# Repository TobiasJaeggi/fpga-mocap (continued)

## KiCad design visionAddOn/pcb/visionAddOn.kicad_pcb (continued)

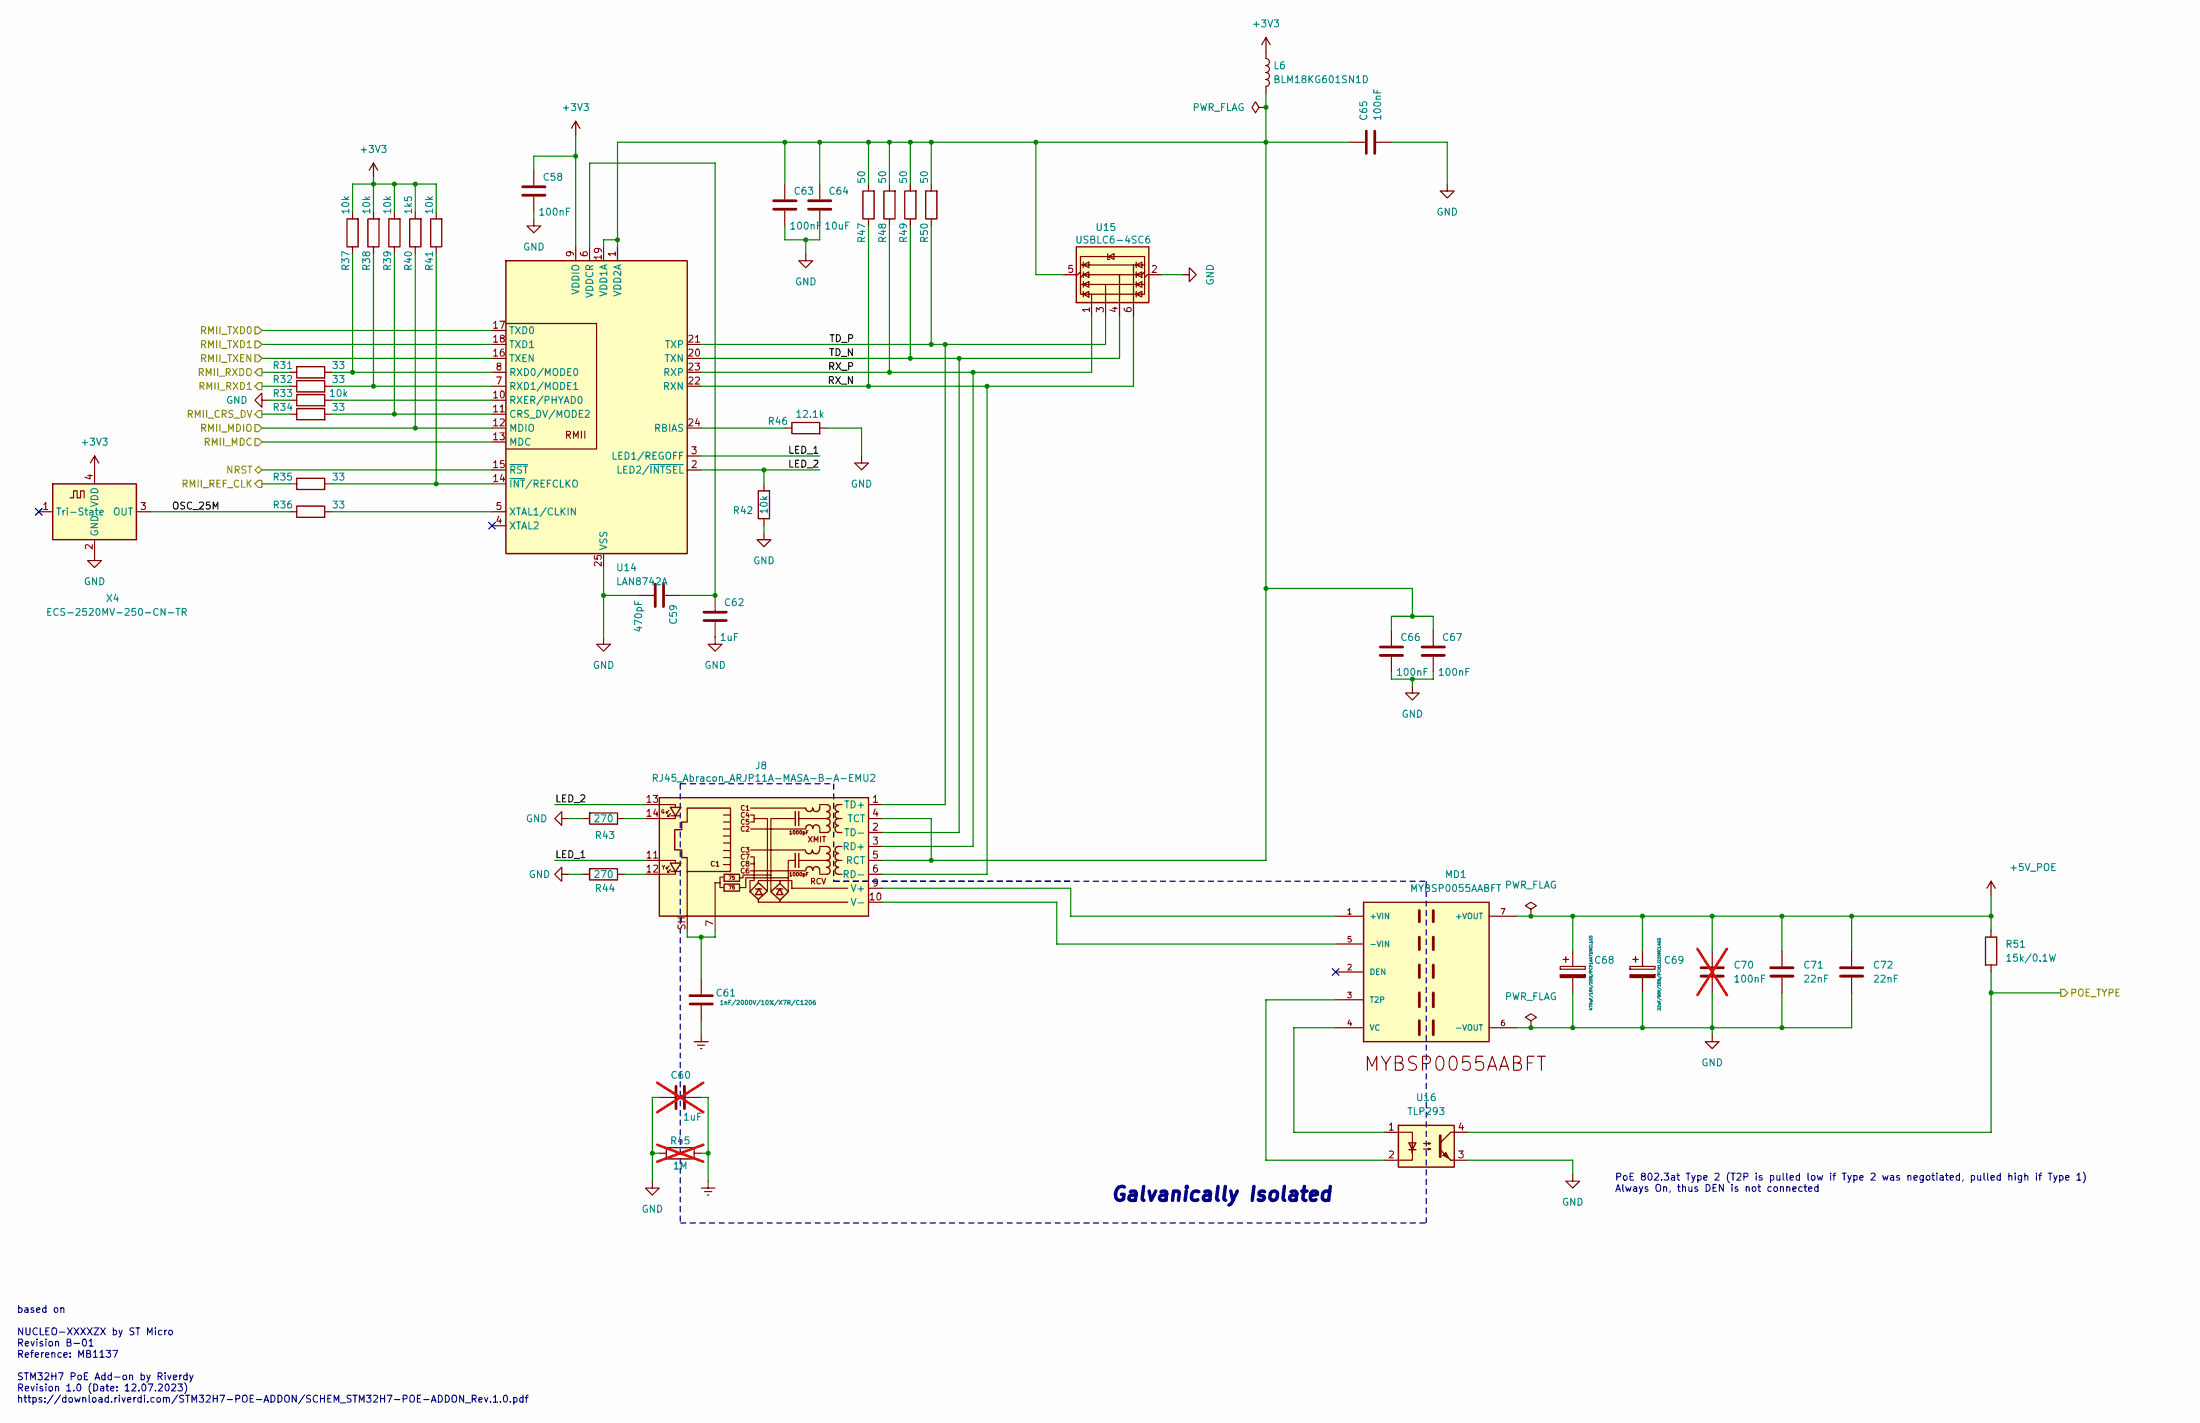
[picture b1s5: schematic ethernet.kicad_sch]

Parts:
C58, C63, C65, C66, C67: 100nF; C_0402_1005Metric; DigiKey-Partnumber 490-6328-2-ND
C59: 470pF; C_0402_1005Metric; DigiKey-Partnumber 490-1300-2-ND
C60: 1uF; C_0402_1005Metric; DigiKey-Partnumber 490-10024-2-ND; not fitted
C61: 1nF/2000V/10%/X7R/C1206; C_1206_3216Metric; DigiKey-Partnumber 709-VPDD202W102K1GV001ETR-ND
C62: 1uF; C_0402_1005Metric; DigiKey-Partnumber 490-10024-2-ND
C64: 10uF; C_0402_1005Metric; DigiKey-Partnumber 490-GRM155R61A106ME11DTR-ND
C68: 470uF/10V/20%/PCF1A471MCL1GS; CP_Elec_10x10; DigiKey-Partnumber 493-2996-2-ND
C69: 22uF/80V/20%/PCH1J220MCL4GS; CP_Elec_6.3x7.7; DigiKey-Partnumber PCH1J220MCL4GTR-ND
C70: 100nF; C_0603_1608Metric; DigiKey-Partnumber 311-1088-2-ND; not fitted
C71, C72: 22nF; C_0603_1608Metric; DigiKey-Partnumber 490-17777-2-ND
J8: RJ45_Abracon_ARJP11A-MASA-B-A-EMU2; RJ45_Abracon_ARJP11A-MA_Horizontal; DigiKey-Partnumber ARJP11A-MASA-B-A-EMU2-ND
L6: BLM18KG601SN1D; L_0603_1608Metric; DigiKey-Partnumber 490-5258-2-ND
MD1: MYBSP0055AABFT; MYBSP0055AABFT_0; DigiKey-Partnumber 811-MYBSP0055AABFTTR-ND
R31, R32, R34, R35, R36: 33; R_0402_1005Metric; DigiKey-Partnumber 311-33.0LRTR-ND
R33, R37, R38, R39, R41, R42: 10k; R_0402_1005Metric; DigiKey-Partnumber 311-10KJRTR-ND
R40: 1k5; R_0402_1005Metric; DigiKey-Partnumber 311-1.5KJRTR-ND
R43, R44: 270; R_0402_1005Metric; DigiKey-Partnumber 541-4842-2-ND
R45: 1M; R_0402_1005Metric; DigiKey-Partnumber 311-1.00MLRTR-ND; not fitted
R46: 12.1k; R_0402_1005Metric; DigiKey-Partnumber 311-12.1KLRTR-ND
R47, R48, R49, R50: 50; R_0402_1005Metric; DigiKey-Partnumber 13-RT0402BRE0750RLTR-ND
R51: 15k/0.1W; R_0402_1005Metric; DigiKey-Partnumber P15.0KLTR-ND
U14: LAN8742A; VQFN-24-1EP_4x4mm_P0.5mm_EP2.5x2.5mm_ThermalVias; DigiKey-Partnumber LAN8742A-CZ-TR-ND
U15: USBLC6-4SC6; SOT-23-6; DigiKey-Partnumber 497-4492-2-ND
U16: TLP293; SOIC-4_4.55x2.6mm_P1.27mm; DigiKey-Partnumber TLP293(GB-TPLETR-ND
X4: ECS-2520MV-250-CN-TR; Oscillator_SMD_ECS_2520MV-xxx-xx-4Pin_2.5x2.0mm; DigiKey-Partnumber XC2752TR-ND

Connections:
+3V3: C58.2, L6.1, R37.2, R38.2, R39.2, R40.2, R41.2, U14.9 (VDDIO), X4.4 (VDD); also elsewhere on the board
+5V_POE: C68.1, C69.1, C70.1, C71.1, C72.1, MD1.7 (+VOUT), R51.1; also elsewhere on the board
/N_RESET: U14.15 (~RST); also elsewhere on the board
/ethernet/LED_1: J8.11, U14.3 (LED1/REGOFF)
/ethernet/LED_2: J8.13, R42.2, U14.2 (LED2/~INTSEL)
/ethernet/OSC_25M: R36.1, X4.3 (OUT)
/ethernet/POE_TYPE: R51.2, U16.4; also elsewhere on the board
/ethernet/RMII_CRS_DV: R34.1; also elsewhere on the board
/ethernet/RMII_MDC: U14.13 (MDC); also elsewhere on the board
/ethernet/RMII_MDIO: R40.1, U14.12 (MDIO); also elsewhere on the board
/ethernet/RMII_REF_CLK: R35.1; also elsewhere on the board
/ethernet/RMII_RXD1: R32.1; also elsewhere on the board
/ethernet/RMII_RXDO: R31.1; also elsewhere on the board
/ethernet/RMII_TXD0: U14.17 (TXD0); also elsewhere on the board
/ethernet/RMII_TXD1: U14.18 (TXD1); also elsewhere on the board
/ethernet/RMII_TXEN: U14.16 (TXEN); also elsewhere on the board
/ethernet/RX_N: J8.6 (RD-), R47.1, U14.22 (RXN), U15.6 (I/O4)
/ethernet/RX_P: J8.3 (RD+), R48.1, U14.23 (RXP), U15.1 (I/O1)
/ethernet/TD_N: J8.2 (TD-), R49.1, U14.20 (TXN), U15.4 (I/O3)
/ethernet/TD_P: J8.1 (TD+), R50.1, U14.21 (TXP), U15.3 (I/O2)
Earth: C60.1, C61.1, R45.1
GND: C58.1, C59.1, C60.2, C62.1, C63.1, C64.1, C65.2, C66.1, C67.1, C68.2, C69.2, C70.2, C71.2, C72.2, MD1.6 (-VOUT), R33.1, R42.1, R43.2, R44.2, R45.2, R46.2, U14.25 (VSS), U15.2 (GND), U16.3, X4.2 (GND); also elsewhere on the board
unnamed: C61.2, J8.7, J8.SH
unnamed: J8.12, R44.1
unnamed: J8.14, R43.1
unnamed: C63.2, C64.2, C65.1, C66.2, C67.2, J8.4 (TCT), J8.5 (RCT), L6.2, R47.2, R48.2, R49.2, R50.2, U14.1 (VDD2A), U14.19 (VDD1A), U15.5 (VBUS)
unnamed: J8.9 (V+), MD1.1 (+VIN)
unnamed: J8.10 (V-), MD1.5 (-VIN)
unnamed: MD1.3 (T2P), U16.2
unnamed: MD1.4 (VC), U16.1
unnamed: R34.2, R39.1, U14.11 (CRS_DV/MODE2)
unnamed: R46.1, U14.24 (RBIAS)
unnamed: R31.2, R37.1, U14.8 (RXD0/MODE0)
unnamed: R32.2, R38.1, U14.7 (RXD1/MODE1)
unnamed: R33.2, U14.10 (RXER/PHYAD0)
unnamed: C59.2, C62.2, U14.6 (VDDCR)
unnamed: R36.2, U14.5 (XTAL1/CLKIN)
unnamed: R35.2, R41.1, U14.14 (~INT/REFCLKO)

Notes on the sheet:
PoE 802.3at Type 2 (T2P is pulled low if Type 2 was negotiated, pulled high if Type 1) Always On, thus DEN is not connected
Galvanically Isolated
based on NUCLEO-XXXXZX by ST Micro Revision B-01 Reference: MB1137 STM32H7 PoE Add-on by Riverdy Revision 1.0 (Date: 12.07.2023) https://download.riverdi.com/STM32H7-POE-ADDON/SCHEM_STM32H7-POE-ADDON_Rev.1.0.pdf

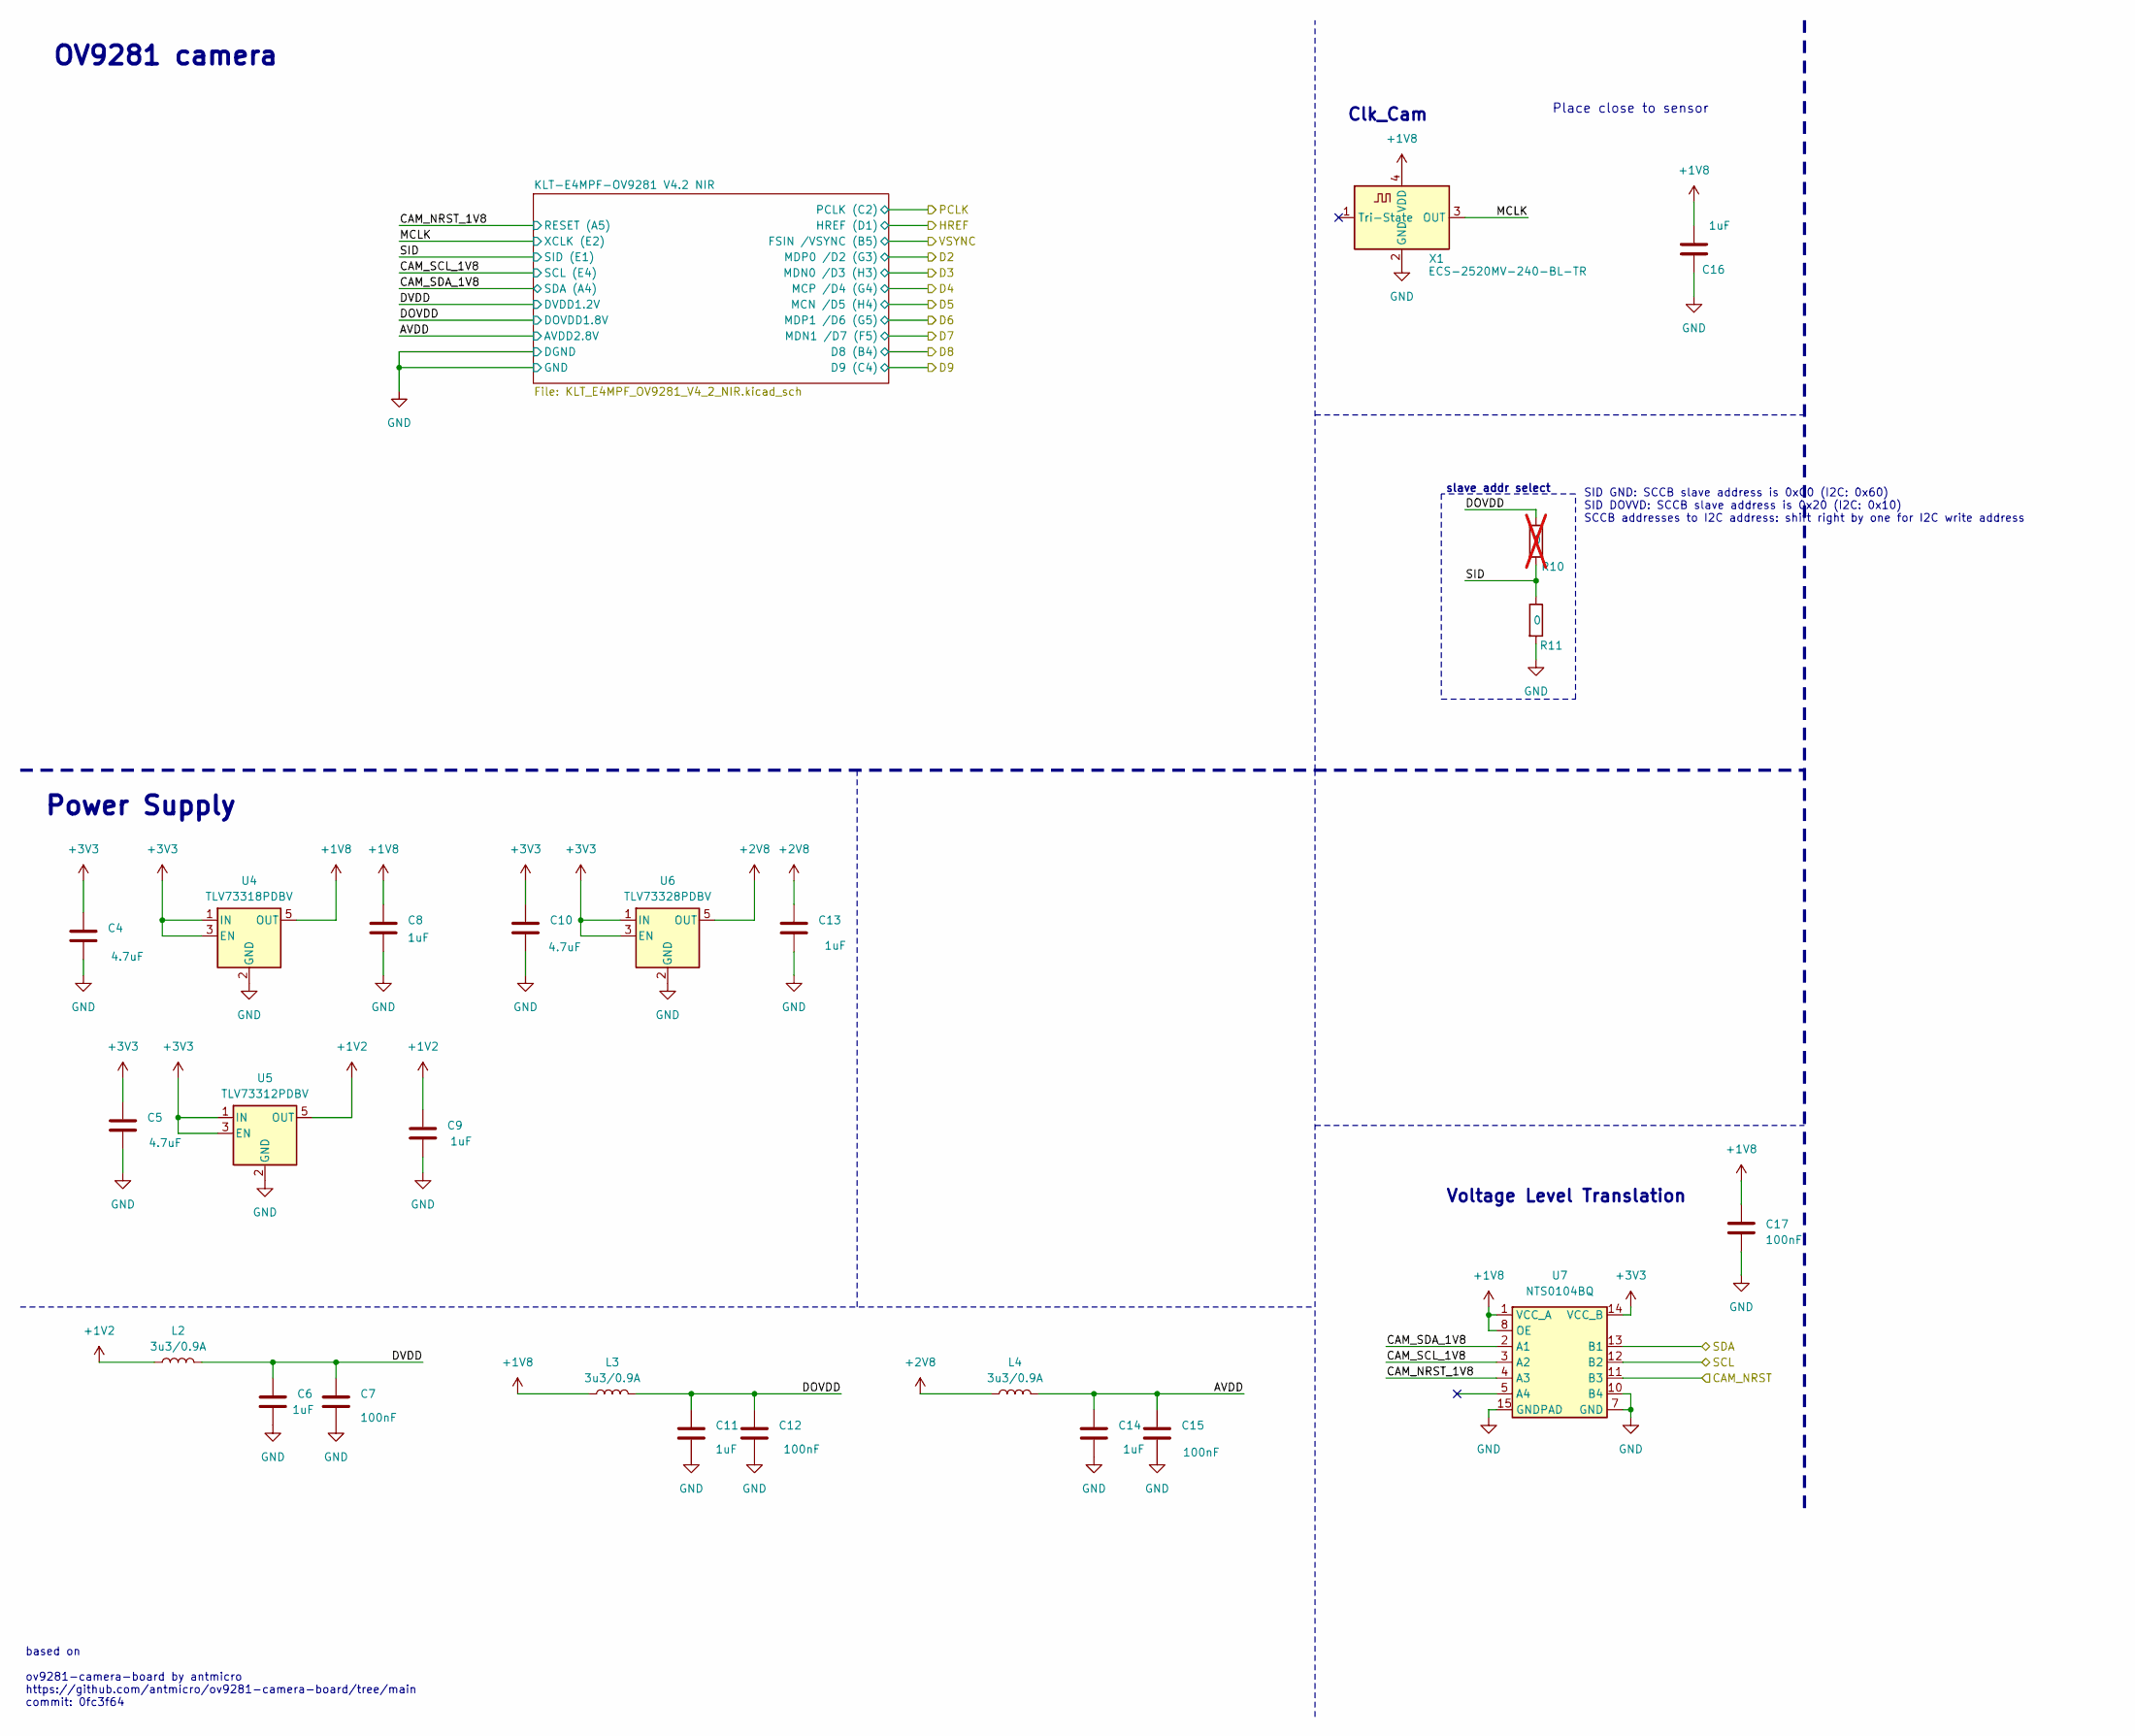
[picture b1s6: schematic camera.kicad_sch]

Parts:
C4, C5, C10: 4.7uF; C_0805_2012Metric; DigiKey-Partnumber 1292-0805X475K250CTTR-ND
C6, C8, C9, C11, C13, C14, C16: 1uF; C_0603_1608Metric; DigiKey-Partnumber 445-4112-2-ND
C7, C12, C15, C17: 100nF; C_0402_1005Metric; DigiKey-Partnumber 490-6328-2-ND
L2, L3, L4: MLP2012S3R3MT; L_0805_2012Metric; DigiKey-Partnumber 445-6365-2-ND
R10: 0; R_0402_1005Metric; DigiKey-Partnumber 311-0.0JRTR-ND; not fitted
R11: 0; R_0402_1005Metric; DigiKey-Partnumber 311-0.0JRTR-ND
U4: TLV73318PDBV; SOT-23-5; DigiKey-Partnumber 296-40669-2-ND
U5: TLV73312PDBV; SOT-23-5; DigiKey-Partnumber 296-40665-2-ND
U6: TLV73328PDBV; SOT-23-5; DigiKey-Partnumber 296-42282-2-ND
U7: NTS0104BQ; DHVQFN-14-1EP_2.5x3mm_P0.5mm_EP1x1.5mm; DigiKey-Partnumber 568-12382-2-ND
X1: ECS-2520MV-240-BL-TR; Oscillator_SMD_ECS_2520MV-xxx-xx-4Pin_2.5x2.0mm; DigiKey-Partnumber 50-ECS-2520MV-240-BL-TR-ND

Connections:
+1V2: C9.1, L2.1, U5.5 (OUT)
+1V8: C8.1, C16.1, C17.1, L3.1, U4.5 (OUT), U7.1 (VCC_A), U7.8 (OE), X1.4 (VDD)
+2V8: C13.1, L4.1, U6.5 (OUT)
+3V3: C4.1, C5.1, C10.1, U4.1 (IN), U4.3 (EN), U5.1 (IN), U5.3 (EN), U6.1 (IN), U6.3 (EN), U7.14 (VCC_B); also elsewhere on the board
/N_RESET: U7.11 (B3); also elsewhere on the board
/SCL_CAM: U7.12 (B2); also elsewhere on the board
/SDA_CAM: U7.13 (B1); also elsewhere on the board
/camera/AVDD: C14.1, C15.1, L4.2; also elsewhere on the board
/camera/CAM_NRST_1V8: U7.4 (A3); also elsewhere on the board
/camera/CAM_SCL_1V8: U7.3 (A2); also elsewhere on the board
/camera/CAM_SDA_1V8: U7.2 (A1); also elsewhere on the board
/camera/DOVDD: C11.1, C12.1, L3.2, R10.1; also elsewhere on the board
/camera/DVDD: C6.1, C7.1, L2.2; also elsewhere on the board
/camera/MCLK: X1.3 (OUT); also elsewhere on the board
/camera/SID: R10.2, R11.1; also elsewhere on the board
GND: C4.2, C5.2, C6.2, C7.2, C8.2, C9.2, C10.2, C11.2, C12.2, C13.2, C14.2, C15.2, C16.2, C17.2, R11.2, U4.2 (GND), U5.2 (GND), U6.2 (GND), U7.7 (GND), U7.10 (B4), U7.15 (GNDPAD), X1.2 (GND); also elsewhere on the board

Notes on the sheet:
Voltage Level Translation
SID GND: SCCB slave address is 0xC0 (I2C: 0x60) SID DOVVD: SCCB slave address is 0x20 (I2C: 0x10) SCCB addresses to I2C address: shift right by one for I2C write address
Power Supply
slave addr select
Clk_Cam
OV9281 camera
Place close to sensor
based on ov9281-camera-board by antmicro https://github.com/antmicro/ov9281-camera-board/tree/main commit: 0fc3f64

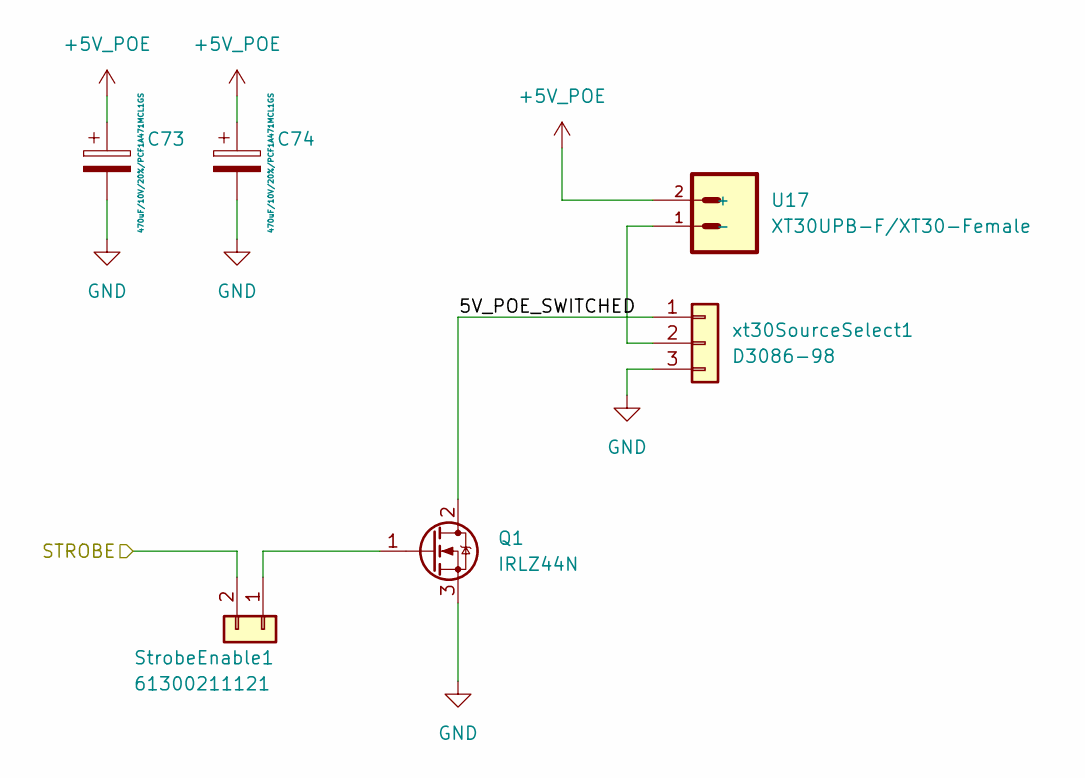
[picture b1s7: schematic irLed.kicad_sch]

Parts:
C73, C74: 470uF/10V/20%/PCF1A471MCL1GS; CP_Elec_10x10; DigiKey-Partnumber 493-2996-2-ND
Q1: IRLZ44N; TO-220-3_Vertical; DigiKey-Partnumber IRLZ44NPBF-ND
StrobeEnable1: 61300211121; PinHeader_1x02_P2.54mm_Vertical; DigiKey-Partnumber 732-5315-ND
U17: XT30UPB-F/XT30-Female; AMASS_XT30UPB-F_1x02_P5.0mm_Vertical; DigiKey-Partnumber 1738-1436-ND
xt30SourceSelect1: D3086-98; HARWIN_D3086-98; DigiKey-Partnumber 952-1864-ND

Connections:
+5V_POE: C73.1, C74.1, U17.2 (+); also elsewhere on the board
/STROBE: StrobeEnable1.2; also elsewhere on the board
/irLed/5V_POE_SWITCHED: Q1.2 (D), xt30SourceSelect1.1
GND: C73.2, C74.2, Q1.3 (S), xt30SourceSelect1.3; also elsewhere on the board
unnamed: Q1.1 (G), StrobeEnable1.1
unnamed: U17.1 (-), xt30SourceSelect1.2

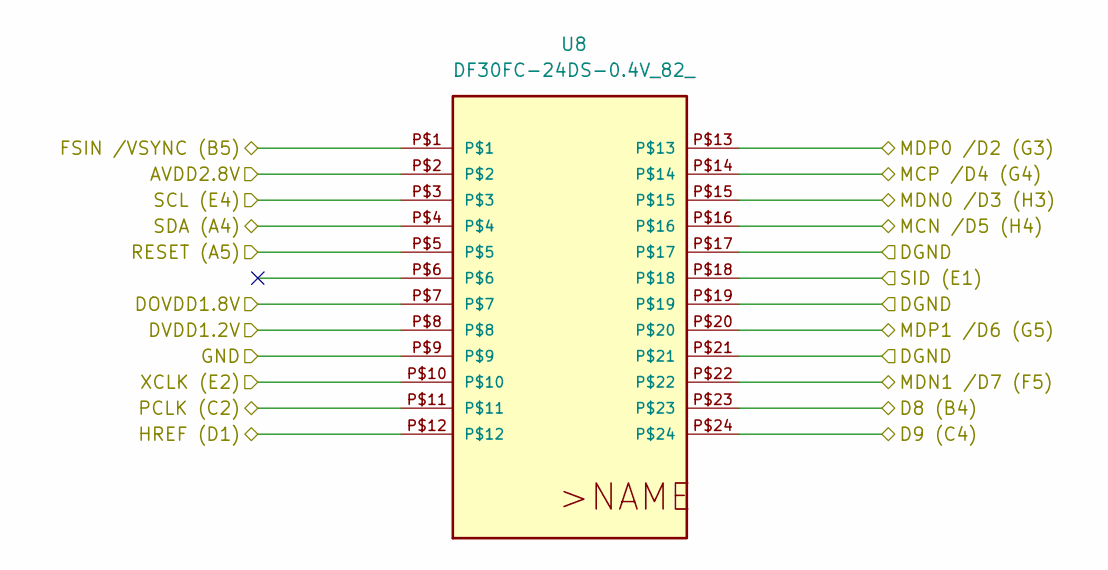
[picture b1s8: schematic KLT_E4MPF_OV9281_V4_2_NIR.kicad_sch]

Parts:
U8: DF30FC-24DS-0.4V_82_; DF30FC-24DS_KLT_PIN_MAPPING; DigiKey-Partnumber H3860TR-ND

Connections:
/D2_CAMERA: U8.P$13; also elsewhere on the board
/D3_CAMERA: U8.P$15; also elsewhere on the board
/D4_CAMERA: U8.P$14; also elsewhere on the board
/D5_CAMERA: U8.P$16; also elsewhere on the board
/D6_CAMERA: U8.P$20; also elsewhere on the board
/D7_CAMERA: U8.P$22; also elsewhere on the board
/D8_CAMERA: U8.P$23; also elsewhere on the board
/D9_CAMERA: U8.P$24; also elsewhere on the board
/HREF_CAMERA: U8.P$12; also elsewhere on the board
/PCLK_CAMERA: U8.P$11; also elsewhere on the board
/VSYNC_CAMERA: U8.P$1; also elsewhere on the board
/camera/AVDD: U8.P$2; also elsewhere on the board
/camera/CAM_NRST_1V8: U8.P$5; also elsewhere on the board
/camera/CAM_SCL_1V8: U8.P$3; also elsewhere on the board
/camera/CAM_SDA_1V8: U8.P$4; also elsewhere on the board
/camera/DOVDD: U8.P$7; also elsewhere on the board
/camera/DVDD: U8.P$8; also elsewhere on the board
/camera/MCLK: U8.P$10; also elsewhere on the board
/camera/SID: U8.P$18; also elsewhere on the board
GND: U8.P$9, U8.P$17, U8.P$19, U8.P$21; also elsewhere on the board

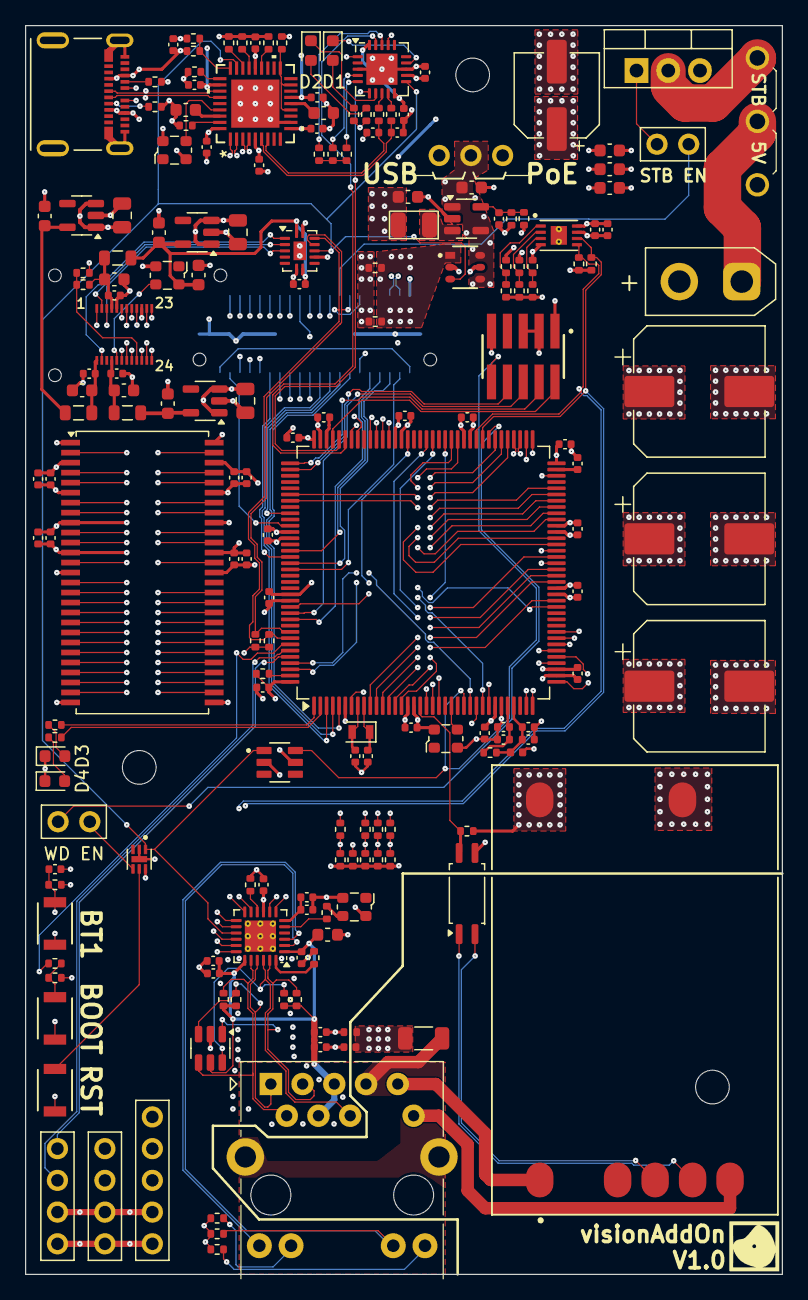
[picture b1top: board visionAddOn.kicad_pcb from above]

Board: 6 copper layers, 60.6 x 100.0 mm, 188 parts (1 on the bottom side), 198 nets.

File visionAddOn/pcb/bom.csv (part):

"Reference","Value","Datasheet","Footprint","Qty","DNP","Description","DigiKey-Partnumber","CUBUS"
"R5","0","~","Resistor_SMD:R_0402_1005Metric","1","","","311-0.0JRTR-ND","0 RESC1005X35"
"R6,R7,R10,R60,R61,R62","0","","Resistor_SMD:R_0402_1005Metric","6","DNP","","311-0.0JRTR-ND","0 RESC1005X35"
"R11,R57,R58,R59","0","","Resistor_SMD:R_0402_1005Metric","4","","","311-0.0JRTR-ND","0 RESC1005X35"
"C31,C33","9pF","~","Capacitor_SMD:C_0402_1005Metric","2","","","490-8232-2-ND",""
"C2","18pF","~","Capacitor_SMD:C_0402_1005Metric","1","","","490-8082-2-ND","18P CAPC1005X50"
"C18,C20","47pF","~","Capacitor_SMD:C_0402_1005Metric","2","","","490-5942-2-ND","47P CAPC1005X50"
"C59","470pF","~","Capacitor_SMD:C_0402_1005Metric","1","","","490-1300-2-ND","470P CAPC1005X50"
"C71,C72","22nF","~","Capacitor_SMD:C_0603_1608Metric","2","","Unpolarized capacitor","490-17777-2-ND",""
"C7,C12,C15","100nF","","Capacitor_SMD:C_0402_1005Metric","3","","","490-6328-2-ND","100N CAPC1005X50"
"C17,C19,C22,C23,C24,C25,C26,C27,C29,C30,C32,C35,C36,C38,C39,C40,C41,C42,C45,C46,C47,C48,C49,C50,C51,C54,C55,C58,C63,C65,C66,C67,C76,C77,C79","100nF","~","Capacitor_SMD:C_0402_1005Metric","35","","","490-6328-2-ND","100N CAPC1005X50"
"C70","100nF","~","Capacitor_SMD:C_0603_1608Metric","1","DNP","Unpolarized capacitor","311-1088-2-ND","100N CAPC1608X80"
"C1,C3","1uF","~","Capacitor_SMD:C_0603_1608Metric","2","","","445-4112-2-ND","1U CAPC1608X80"
"C6,C8,C9,C11,C13,C14,C16","1uF","","Capacitor_SMD:C_0603_1608Metric","7","","","445-4112-2-ND","1U CAPC1608X80"
"C34,C37,C52,C53,C56,C57,C62,C75","1uF","~","Capacitor_SMD:C_0402_1005Metric","8","","","490-10024-2-ND","1U CAPC1005X50"
"C60","1uF","~","Capacitor_SMD:C_0402_1005Metric","1","DNP","","490-10024-2-ND","1U CAPC1005X50"
"C43,C44","2.2uF","~","Capacitor_SMD:C_0402_1005Metric","2","","","490-10012-2-ND","2U2 CAPC1005X50"
"C4,C5,C10","4.7uF","","Capacitor_SMD:C_0805_2012Metric","3","","","1292-0805X475K250CTTR-ND","4u7 CAPC2012X95"
"C21","10uF","~","Capacitor_SMD:C_0603_1608Metric","1","","","445-4112-2-ND",""
"C64","10uF","~","Capacitor_SMD:C_0402_1005Metric","1","","","490-GRM155R61A106ME11DTR-ND",""
"R14,R15","27","~","Resistor_SMD:R_0402_1005Metric","2","","","P27.0LTR-ND","27 RESC1005X35"
"R31,R32,R34,R35,R36","33","~","Resistor_SMD:R_0402_1005Metric","5","","","311-33.0LRTR-ND",""
"R30","47","~","Resistor_SMD:R_0402_1005Metric","1","","","RMCF0402JT47R0TR-ND",""
"R47,R48,R49,R50","50","~","Resistor_SMD:R_0402_1005Metric","4","","","13-RT0402BRE0750RLTR-ND",""
"R16,R17,R43,R44","270","~","Resistor_SMD:R_0402_1005Metric","4","","","541-4842-2-ND","270 RESC1005X35"
"R1,R2,R28,R29","1k","~","Resistor_SMD:R_0402_1005Metric","4","","","311-1.0KJRTR-ND","1K RESC1005X35"
"R8,R9","1k","~","Resistor_SMD:R_0402_1005Metric","2","","Resistor","311-1.0KJRTR-ND","1K RESC1005X35"
"R18,R19,R20,R21,R22,R26,R27,R33,R37,R38,R39,R41,R42,R52,R53,R54,R55","10k","~","Resistor_SMD:R_0402_1005Metric","17","","","311-10KJRTR-ND","10K RESC1005X35"
"R23","12k","~","Resistor_SMD:R_0402_1005Metric","1","","","311-12KJRTR-ND","12K RESC1005X35"
"R46","12.1k","~","Resistor_SMD:R_0402_1005Metric","1","","","311-12.1KLRTR-ND",""
"R24,R25","100k","~","Resistor_SMD:R_0402_1005Metric","2","","","311-100KLRTR-ND","100K RESC1005X35"
"R4","150k","~","Resistor_SMD:R_0402_1005Metric","1","","","311-150KLRTR-ND","150K RESC1005X35"
"R3","680k","~","Resistor_SMD:R_0402_1005Metric","1","","","311-680KJRTR-ND","680K RESC1005X35"
"R45","1M","~","Resistor_SMD:R_0402_1005Metric","1","DNP","","311-1.00MLRTR-ND","1M RESC1005X35"
"StrobeEnable1","61300211121","~","Connector_PinHeader_2.54mm:PinHeader_1x02_P2.54mm_Vertical","1","","Generic connector, single row, 01x02, script generated (kicad-library-utils/schlib/autogen/connector/)","732-5315-ND",""
"WATCHDOG_ENABLE1","61300211121","https://www.we-online.com/components/products/datasheet/6130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","Connector_PinHeader_2.54mm:PinHeader_1x02_P2.54mm_Vertical","1","","Generic connector, single row, 01x02, script generated (kicad-library-utils/schlib/autogen/connector/)","732-5315-ND",""
"J3","61300311121","~","Connector_PinHeader_2.54mm:PinHeader_1x03_P2.54mm_Vertical","1","","Generic connector, single row, 01x03, script generated (kicad-library-utils/schlib/autogen/connector/)","732-5316-ND",""
"J1,J7","61300411121","~","Connector_PinHeader_2.54mm:PinHeader_1x04_P2.54mm_Vertical","2","","Generic connector, single row, 01x04, script generated (kicad-library-utils/schlib/autogen/connector/)","732-5317-ND",""
"J5","61300511121","~","Connector_PinHeader_2.54mm:PinHeader_1x05_P2.54mm_Vertical","1","","Generic connector, single row, 01x05, script generated (kicad-library-utils/schlib/autogen/connector/)","732-5318-ND",""
"J4","105450-0101","https://tools.molex.com/pdm_docs/ps/PS-105448-001.pdf","visionAddOn:MOLEX_105450-0101","1","","USB Shielded I/O Receptacle; Type C; Right Angle; Surface Mount; Gold over Nickel","WM12856TR-ND",""
"D2,D4","150060GS75020","https://www.we-online.com/components/products/datasheet/1500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","LED_SMD:LED_0603_1608Metric","2","","Light emitting diode","732-150060GS75020TR-ND",""
"D1,D3","150060RS75020","https://www.we-online.com/components/products/datasheet/1500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","LED_SMD:LED_0603_1608Metric","2","","Light emitting diode","732-150060RS75020TR-ND",""
"R51","15k/0.1W","~","Resistor_SMD:R_0402_1005Metric","1","","Resistor","P15.0KLTR-ND",""
"R40","1k5","~","Resistor_SMD:R_0402_1005Metric","1","","","311-1.5KJRTR-ND",""
"L5","1k @ 100MHz/LRC0402CS2N2GV001T","~","Inductor_SMD:L_0402_1005Metric","1","","","712-LRC0402CS2N2GV001TTR-ND",""
"C61","1nF/2000V/10%/X7R/C1206","~","Capacitor_SMD:C_1206_3216Metric","1","","Unpolarized capacitor","709-VPDD202W102K1GV001ETR-ND",""
"C69","22uF/80V/20%/PCH1J220MCL4GS","https://www.nichicon.co.jp/english/series_items/catalog_pdf/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","Capacitor_SMD:CP_Elec_6.3x7.7","1","","Polarized capacitor","PCH1J220MCL4GTR-ND",""
"C68,C73,C74","470uF/10V/20%/PCF1A471MCL1GS","https://www.nichicon.co.jp/english/series_items/catalog_pdf/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","Capacitor_SMD:CP_Elec_10x10","3","","Polarized capacitor","493-2996-2-ND",""
"R12,R13","5k1","~","Resistor_SMD:R_0402_1005Metric","2","","","311-5.10KLRTR-ND",""
"U2","AP2281-3WG-7","~","visionAddOn:SOT26_DIO","1","","","AP2281-3WG-7DITR-ND",""
"U13","AS4C16M16SA","https://www.alliancememory.com/wp-content/uploads/pdf/dram/2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","Package_SO:TSOP-II-54_22.2x10.16mm_P0.8mm","1","","64M – (16M x 16 bit) Synchronous DRAM (SDRAM), TSOP-II-54","1450-1252-ND",""
"U18","AT24C02D-MAHM-T","https://ww1.microchip.com/downloads/aemDocuments/documents/O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","visionAddOn:AT24C02D-MAHM-T_SON50P200X300X60-9N","1","","","AT24C02D-MAHM-TTR-ND",""
"BOOT_STM1","B3U-1000P","~","visionAddOn:SW_B3U-1000P_OMR","1","","https://omronfs.omron.com/en_US/ecb/products/pdf/en-b3u.pdf","SW1020TR-ND",""
"BT1","B3U-1000P","https://omronfs.omron.com/en_US/ecb/products/pdf/en-b3u.pdf","visionAddOn:SW_B3U-1000P_OMR","1","","","SW1020TR-ND",""
"RESET1","B3U-1000P","https://omronfs.omron.com/en_US/ecb/products/pdf/en-b3u.pdf","visionAddOn:SW_B3U-1000P_OMR","1","","","SW1020TR-ND",""
"L6","BLM18KG601SN1D","~","Inductor_SMD:L_0603_1608Metric","1","","Inductor","490-5258-2-ND",""
"C28","C1608X5R0J106M080AB","~","Capacitor_SMD:C_0603_1608Metric","1","","","445-4112-2-ND",""
"xt30SourceSelect1","D3086-98","~","visionAddOn:HARWIN_D3086-98","1","","Generic connector, single row, 01x03, script generated (kicad-library-utils/schlib/autogen/connector/)","952-1864-ND",""
"U8","DF30FC-24DS-0.4V_82_","https://www.hirose.com/product/document?clcode=CL0684-1276-0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","visionAddOn:DF30FC-24DS_KLT_PIN_MAPPING","1","","","H3860TR-ND",""
"X1","ECS-2520MV-240-BL-TR","https://www.ecsxtal.com/store/pdf/ECS-2520MV.pdf","Oscillator:Oscillator_SMD_ECS_2520MV-xxx-xx-4Pin_2.5x2.0mm","1","","HCMOS Crystal Clock Oscillator, 2.5x2.0 mm SMD","50-ECS-2520MV-240-BL-TR-ND",""
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
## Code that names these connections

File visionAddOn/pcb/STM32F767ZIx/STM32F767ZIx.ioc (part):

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Mcu.Name=STM32F767ZITx
Mcu.Package=LQFP144
Mcu.UserName=STM32F767ZITx
PA0/WKUP.GPIOParameters=GPIO_Label
PA0/WKUP.GPIO_Label=STM_DBG_10
PA0/WKUP.Signal=GPIO_Input
PA1.Mode=RMII
PA1.Signal=ETH_REF_CLK
PA10.Mode=Asynchronous
PA10.Signal=USART1_RX
PA11.Mode=CTS_RTS
PA11.Signal=USART1_CTS
PA12.Mode=CTS_RTS
PA12.Signal=USART1_RTS
PA13.GPIOParameters=GPIO_Label
PA13.GPIO_Label=TMS
PA13.Signal=SYS_JTMS-SWDIO
PA14.GPIOParameters=GPIO_Label
PA14.GPIO_Label=TCK
PA14.Signal=SYS_JTCK-SWCLK
PA15.Signal=SYS_JTDI
PA2.Mode=RMII
PA2.Signal=ETH_MDIO
PA3.Mode=Asynchronous
PA3.Signal=USART2_RX
PA4.Mode=Slave_8_bits_External_Synchro
PA4.Signal=DCMI_HSYNC
PA5.Mode=Full_Duplex_Master
PA5.Signal=SPI1_SCK
PA6.Mode=Slave_8_bits_External_Synchro
PA6.Signal=DCMI_PIXCLK
PA7.Mode=RMII
PA7.Signal=ETH_CRS_DV
PA8.GPIOParameters=GPIO_Label
PA8.GPIO_Label=STM_DBG_11
PA8.Signal=GPIO_Input
PA9.Mode=Asynchronous
PA9.Signal=USART1_TX
PB0.GPIOParameters=GPIO_Label
PB0.GPIO_Label=STM_DBG_15
PB0.Signal=GPIO_Input
PB1.GPIOParameters=GPIO_Label
PB1.GPIO_Label=STM_DBG_16
PB1.Signal=GPIO_Input
PB10.GPIOParameters=GPIO_Label
PB10.GPIO_Label=STM_DBG_21
PB10.Signal=GPIO_Input
PB11.Mode=RMII
PB11.Signal=ETH_TX_EN
PB12.Mode=RMII
PB12.Signal=ETH_TXD0
PB13.Mode=RMII
PB13.Signal=ETH_TXD1
PB14.Mode=Device_Only_FS
PB14.Signal=USB_OTG_HS_DM
PB15.Mode=Device_Only_FS
PB15.Signal=USB_OTG_HS_DP
PB2.GPIOParameters=GPIO_Label
PB2.GPIO_Label=STM_DBG_17
PB2.Signal=GPIO_Input
PB3.GPIOParameters=GPIO_Label
PB3.GPIO_Label=SWO
PB3.Signal=SYS_JTDO-SWO
PB4.Mode=Full_Duplex_Master
PB4.Signal=SPI1_MISO
PB5.GPIOParameters=GPIO_Label
PB5.GPIO_Label=STM_DBG_18
PB5.Signal=GPIO_Input
PB6.Mode=I2C
PB6.Signal=I2C1_SCL
PB7.Mode=I2C
PB7.Signal=I2C1_SDA
PB8.Mode=Asynchronous
PB8.Signal=UART5_RX
PB9.Mode=Asynchronous
PB9.Signal=UART5_TX
PC0.Signal=FMC_SDNWE
PC1.Mode=RMII
PC1.Signal=ETH_MDC
PC10.GPIOParameters=GPIO_Label
PC10.GPIO_Label=STM_DBG_23
PC10.Signal=GPIO_Input
PC11.GPIOParameters=GPIO_Label
PC11.GPIO_Label=STM_DBG_24
PC11.Signal=GPIO_Input
PC12.GPIOParameters=GPIO_Label
PC12.GPIO_Label=STM_DBG_20
PC12.Signal=GPIO_Input
PC13.GPIOParameters=GPIO_Label
PC13.GPIO_Label=BUTTON1
PC13.Signal=GPIO_Input
PC14/OSC32_IN.Mode=LSE-External-Oscillator
PC14/OSC32_IN.Signal=RCC_OSC32_IN
PC15/OSC32_OUT.Mode=LSE-External-Oscillator
PC15/OSC32_OUT.Signal=RCC_OSC32_OUT
PC2.Mode=SdramChipSelect1_1
PC2.Signal=FMC_SDNE0
PC3.Mode=SdramChipSelect1_1
PC3.Signal=FMC_SDCKE0
PC4.Mode=RMII
PC4.Signal=ETH_RXD0
PC5.Mode=RMII
PC5.Signal=ETH_RXD1
PC6.Mode=Slave_8_bits_External_Synchro
PC6.Signal=DCMI_D0
PC7.Mode=Slave_8_bits_External_Synchro
PC7.Signal=DCMI_D1
PC8.Mode=Slave_8_bits_External_Synchro
PC8.Signal=DCMI_D2
PC9.Mode=Slave_8_bits_External_Synchro
PC9.Signal=DCMI_D3
PD0.Signal=FMC_D2_DA2
PD1.Signal=FMC_D3_DA3
PD10.Signal=FMC_D15_DA15
PD11.GPIOParameters=GPIO_Label
PD11.GPIO_Label=WATCHDOG
PD11.Signal=GPIO_Output
PD12.Mode=I2C
PD12.Signal=I2C4_SCL
PD13.Mode=I2C
PD13.Signal=I2C4_SDA
PD14.Signal=FMC_D0_DA0
PD15.Signal=FMC_D1_DA1
PD2.GPIOParameters=GPIO_Label
PD2.GPIO_Label=STM_DBG_19
PD2.Signal=GPIO_Input
PD3.Mode=Slave_8_bits_External_Synchro
PD3.Signal=DCMI_D5
PD4.GPIOParameters=GPIO_Label
PD4.GPIO_Label=STM_DBG_8
PD4.Signal=GPIO_Input
PD5.Mode=Asynchronous
PD5.Signal=USART2_TX
PD6.GPIOParameters=GPIO_Label
PD6.GPIO_Label=STM_DGB_25
PD6.Signal=GPIO_Input
PD7.Mode=Full_Duplex_Master
PD7.Signal=SPI1_MOSI
PD8.Signal=FMC_D13_DA13
PD9.Signal=FMC_D14_DA14
PE0.Signal=FMC_NBL0
PE1.Signal=FMC_NBL1
PE10.Signal=FMC_D7_DA7
PE11.Signal=FMC_D8_DA8
PE12.Signal=FMC_D9_DA9
PE13.Signal=FMC_D10_DA10
PE14.Signal=FMC_D11_DA11
PE15.Signal=FMC_D12_DA12
PE2.GPIOParameters=GPIO_Label
PE2.GPIO_Label=LED_RED
PE2.Signal=GPIO_Output
PE3.GPIOParameters=GPIO_Label
PE3.GPIO_Label=LED_GREEN
PE3.Signal=GPIO_Output
PE4.Mode=Slave_8_bits_External_Synchro
PE4.Signal=DCMI_D4
PE5.Mode=Slave_8_bits_External_Synchro
PE5.Signal=DCMI_D6
PE6.Mode=Slave_8_bits_External_Synchro
PE6.Signal=DCMI_D7
PE7.Signal=FMC_D4_DA4
PE8.Signal=FMC_D5_DA5
PE9.Signal=FMC_D6_DA6
PF0.Signal=FMC_A0
PF1.Signal=FMC_A1
PF10.GPIOParameters=GPIO_Label
PF10.GPIO_Label=STM_DBG_9
PF10.Signal=GPIO_Input
PF11.Signal=FMC_SDNRAS
PF12.Signal=FMC_A6
PF13.Signal=FMC_A7
PF14.Signal=FMC_A8
PF15.Signal=FMC_A9
PF2.Signal=FMC_A2
PF3.Signal=FMC_A3
PF4.Signal=FMC_A4
PF5.Signal=FMC_A5
PF6.GPIOParameters=GPIO_Label
PF6.GPIO_Label=POE_TYPE
PF6.Signal=GPIO_Input
PF7.Mode=Full_Duplex_Master
PF7.Signal=SPI5_SCK
PF8.Mode=Full_Duplex_Master
PF8.Signal=SPI5_MISO
PF9.Mode=Full_Duplex_Master
PF9.Signal=SPI5_MOSI
PG0.Signal=FMC_A10
PG1.Signal=FMC_A11
PG10.GPIOParameters=GPIO_Label
PG10.GPIO_Label=STM_DBG_3
PG10.Signal=GPIO_Input
PG11.GPIOParameters=GPIO_Label
PG11.GPIO_Label=STM_DBG_4
PG11.Signal=GPIO_Input
PG12.GPIOParameters=GPIO_Label
PG12.GPIO_Label=STM_DBG_5
PG12.Signal=GPIO_Input
PG13.GPIOParameters=GPIO_Label
PG13.GPIO_Label=STM_DBG_6
PG13.Signal=GPIO_Input
PG14.GPIOParameters=GPIO_Label
PG14.GPIO_Label=STM_DBG_7
PG14.Signal=GPIO_Input
PG15.Signal=FMC_SDNCAS
PG2.Signal=FMC_A12
PG3.GPIOParameters=GPIO_Label
PG3.GPIO_Label=STM_DBG_0
PG3.Signal=GPIO_Input
PG4.Signal=FMC_A14_BA0
PG5.Signal=FMC_A15_BA1
PG6.GPIOParameters=GPIO_Label
PG6.GPIO_Label=STM_DBG_1
PG6.Signal=GPIO_Input
PG7.GPIOParameters=GPIO_Label
PG7.GPIO_Label=STM_DBG_2
PG7.Signal=GPIO_Input
PG8.Signal=FMC_SDCLK
PG9.Mode=Slave_8_bits_External_Synchro
PG9.Signal=DCMI_VSYNC
PH0/OSC_IN.Mode=HSE-External-Clock-Source
PH0/OSC_IN.Signal=RCC_OSC_IN
PH1/OSC_OUT.Mode=HSE-External-Clock-Source
PH1/OSC_OUT.Signal=RCC_OSC_OUT
RCC.HSE_VALUE=24000000
RCC.SYSCLKFreq_VALUE=96000000
RCC.SYSCLKSource=RCC_SYSCLKSOURCE_PLLCLK
RCC.SYSCLKSourceVirtual=RCC_SYSCLKSOURCE_PLLCLK
board=NUCLEO-F767ZI
boardIOC=true

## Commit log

2025-07-20 add sources
2025-07-20 add README.md, doc and STL files
2025-07-20 lower resolution and frame rate of demo GIF
